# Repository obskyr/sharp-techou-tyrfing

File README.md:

# The Sharp Techō Tyrfing

The Sharp Techō Tyrfing&nbsp;– a **breakout board for the cartridge slot of** [**Sharp’s **SC Denshi System Techō** line of late-’80s-to-early-’90s PDAs**](https://forums.insertcredit.com/t/stay-sharp-with-sc-denshi-system-techo-games/2326). (Also licensed to other companies&nbsp;– the “Sharp” in the name of this project only coyly alludes to the company name, but formally, it means that this sword-lookin’ PCB is *sharp,* baby. It should fit in SC Denshi System Techō devices by other companies as well!)

The BOM is simple:

* A 45-position single-row female SMD pin header with 1-mm pitch (difficult to find, but a cuttable 50-position one may be available&nbsp;– or do as I did and use two [20-position ones](https://www.digikey.se/short/rdtnbf29) and one [5-position one](https://www.digikey.se/short/3pb4vt48))
* A 45-position single-row male SMD pin header with 1-mm pitch (difficult to find, but a cuttable 50-position one may be available&nbsp;– or do as I did and use two [20-position ones](https://www.digikey.se/short/3jd777nn) and one [5-position one](https://www.digikey.se/short/nfp4mr47))
* A [50-position two-row IDC connector](https://www.digikey.se/short/5dqqh2z7) or [50-position male through-hole pin header with 2.54-mm pitch](https://www.digikey.se/short/1vptfzbh) (and you may want to get [an IDC cable to match](https://www.digikey.se/short/q9n8nwvb))

Worth noting is that the Sharp Techō Tyrfing must be manufactured as a **0.6 mm thick PCB**&nbsp;– otherwise it won’t fit quite right in the machine. For manufacture, download the Gerber files from [the latest release](https://github.com/obskyr/sharp-techou-tyrfing/releases/latest) on GitHub.

Naturally, feel more than free to contact me with any questions!

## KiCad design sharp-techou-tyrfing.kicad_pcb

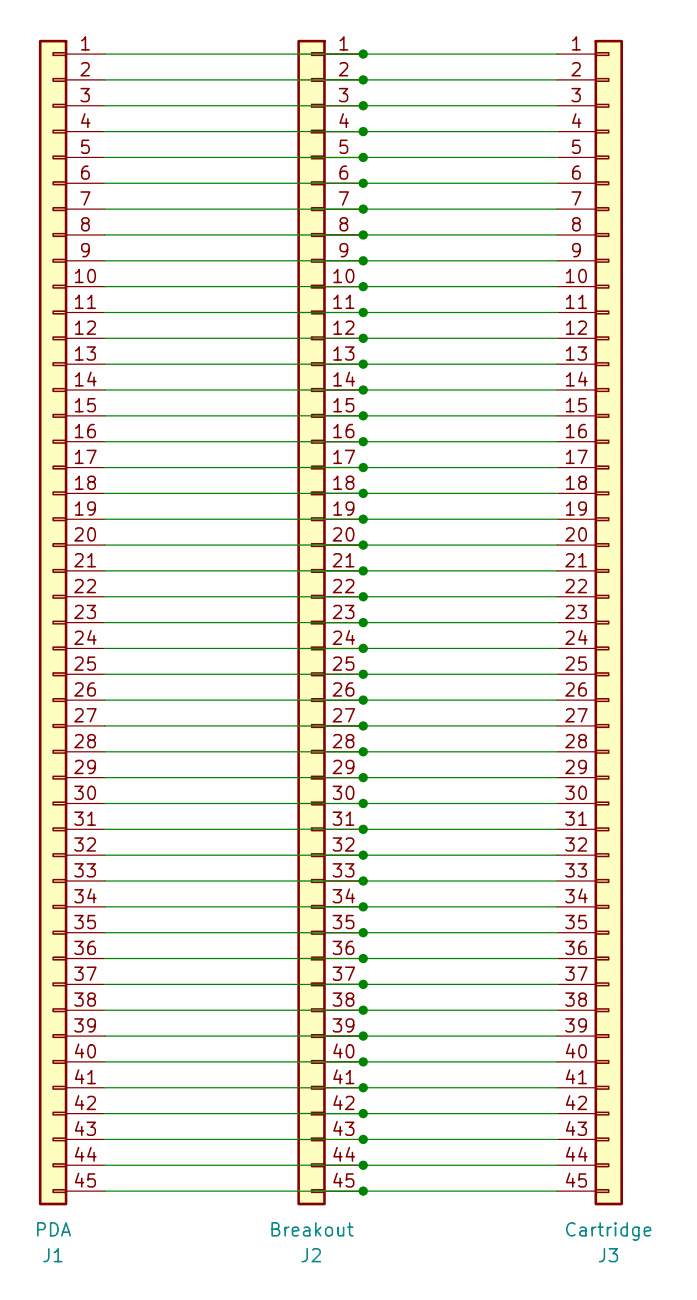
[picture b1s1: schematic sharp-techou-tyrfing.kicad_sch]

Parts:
J1: PDA; PinSocket_1x45_P1.00mm_Horizontal_SMD
J2: Breakout; IDC-Header_2x25_P2.54mm_Vertical
J3: Cartridge; PinHeader_1x45_P1.00mm_Horizontal_SMD

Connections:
unnamed: J1.1, J2.1, J3.1
unnamed: J1.2, J2.2, J3.2
unnamed: J1.3, J2.3, J3.3
unnamed: J1.4, J2.4, J3.4
unnamed: J1.5, J2.5, J3.5
unnamed: J1.6, J2.6, J3.6
unnamed: J1.7, J2.7, J3.7
unnamed: J1.8, J2.8, J3.8
unnamed: J1.9, J2.9, J3.9
unnamed: J1.10, J2.10, J3.10
unnamed: J1.11, J2.11, J3.11
unnamed: J1.12, J2.12, J3.12
unnamed: J1.13, J2.13, J3.13
unnamed: J1.14, J2.14, J3.14
unnamed: J1.15, J2.15, J3.15
unnamed: J1.16, J2.16, J3.16
unnamed: J1.17, J2.17, J3.17
unnamed: J1.18, J2.18, J3.18
unnamed: J1.19, J2.19, J3.19
unnamed: J1.20, J2.20, J3.20
unnamed: J1.21, J2.21, J3.21
unnamed: J1.22, J2.22, J3.22
unnamed: J1.23, J2.23, J3.23
unnamed: J1.24, J2.24, J3.24
unnamed: J1.25, J2.25, J3.25
unnamed: J1.26, J2.26, J3.26
unnamed: J1.27, J2.27, J3.27
unnamed: J1.28, J2.28, J3.28
unnamed: J1.29, J2.29, J3.29
unnamed: J1.30, J2.30, J3.30
unnamed: J1.31, J2.31, J3.31
unnamed: J1.32, J2.32, J3.32
unnamed: J1.33, J2.33, J3.33
unnamed: J1.34, J2.34, J3.34
unnamed: J1.35, J2.35, J3.35
unnamed: J1.36, J2.36, J3.36
unnamed: J1.37, J2.37, J3.37
unnamed: J1.38, J2.38, J3.38
unnamed: J1.39, J2.39, J3.39
unnamed: J1.40, J2.40, J3.40
unnamed: J1.41, J2.41, J3.41
unnamed: J1.42, J2.42, J3.42
unnamed: J1.43, J2.43, J3.43
unnamed: J1.44, J2.44, J3.44
unnamed: J1.45, J2.45, J3.45

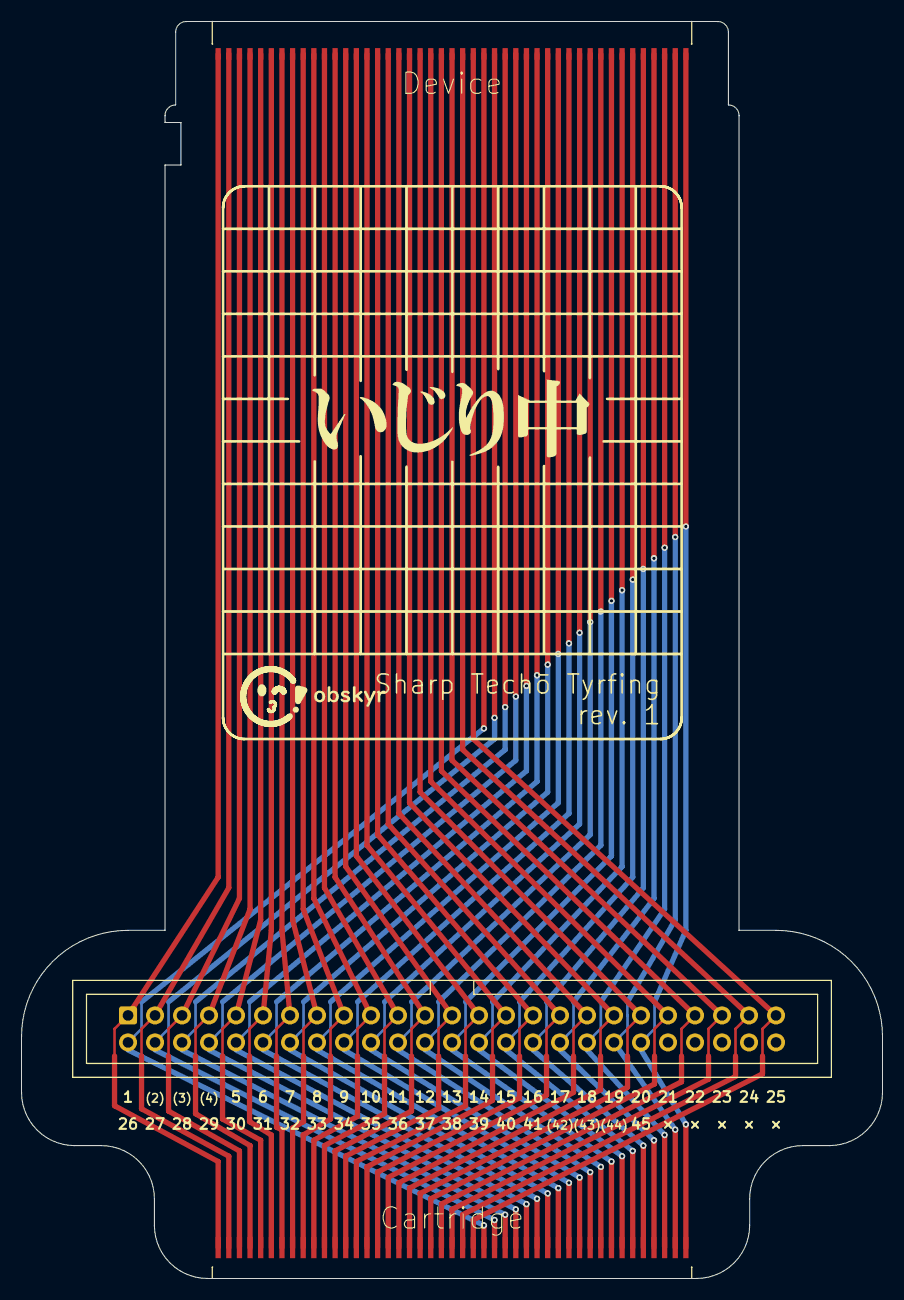
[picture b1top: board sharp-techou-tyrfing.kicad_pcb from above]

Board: 2 copper layers, 81.0 x 118.2 mm, 3 parts (0 on the bottom side), 45 nets.

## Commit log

2024-11-25 It all.
2024-11-27 Added license.
2024-11-27 Set board thickness; added link to manufacturing files in readme.
2024-11-27 Added Open Source Hardware logo; moved name and revision to a text element.
